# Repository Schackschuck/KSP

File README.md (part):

# KSP Cockpit

Controle físico (painel + joystick + telemetria) para o **Kerbal Space Program 1**, feito do zero com hardware e software próprios.

O objetivo principal é **aprender firmware/embarcados e eletrônica**, e de quebra ter um cockpit de verdade — com direito a um botão que dispara um script de pouso autônomo estilo SpaceX.

---

## Arquitetura

```
 PC com Windows: KSP 1 + servidor kRPC
          ▲
          │  cabo de rede direto, com IP fixo (kRPC, TCP/protobuf)
          │  (pela Wi-Fi de casa durante o desenvolvimento)
          ▼
 Raspberry Pi 4 = computador de bordo ............... bridge/
   • ponte kRPC ⇄ placas, aberta sozinha quando o Pi liga
   • tela multifunção no navegador do tablet ........ bridge/celular/
   • dispara os scripts de voo ....................... scripts/
          ▲                         ▲
          │ USB/serial              │ Wi-Fi de casa
          │ (protocolo próprio)     │ (página da tela, por HTTP)
          ▼                         ▼
 Arduino Mega = I/O do painel    tablet = tela multifunção
 firmware/painel/                (Galaxy Tab S 8.4, no Chrome)
          ▲
          │  SPI + linhas analógicas
          ▼
 Backplane: 12 slots ................................ hardware/backplane/
          ▲
          │  um cabo flat de 16 vias por módulo
          ▼
 Módulos do painel, um por seção .......... hardware/modulo_pequeno/, _medio/ e _grande/
   pequeno: 8 entradas + 8 LEDs (1 × 74HC165 + 1 × 74HC595)
   médio: 16 entradas + 24 LEDs (2 × 74HC165 + 3 × 74HC595), com 12 jacks de korry
   grande: 24 entradas + 16 LEDs (3 × 74HC165 + 2 × 74HC595)
   korry, botões, LEDs, sidestick, acelerador
```

Cada parte tem um papel bem definido:

| Parte | Responsabilidade | Não faz |
|---|---|---|
| **KSP + kRPC** (PC) | Expõe o estado da nave e aceita comandos. | — |
| **Computador de bordo** (Raspberry Pi 4, Python) | Conecta no kRPC pela rede, abre *streams* de telemetria, traduz eventos do painel em comandos do jogo e telemetria em mensagens para o painel. Desenha a tela de telemetria. Dispara os scripts de voo de `scripts/` (ex.: pouso autônomo). | Não lê pino nenhum. |
| **Sidestick** (joystick JH-D400X-R4 no painel, lido pelo Mega) | Manda os 3 eixos e o botão como qualquer controle do painel; a ponte os traduz em comandos do kRPC. | O KSP não enxerga o joystick: tudo passa pela ponte. |
| **Painel** (Arduino Mega, C++) | Lê entradas (com debounce), envia eventos; recebe valores e atualiza LEDs, displays e ponteiros. | **Não sabe que o KSP existe.** É um painel de I/O genérico. |
| **Celular** (opcional, página no navegador) | Mostra a tela multifunção pelo Wi-Fi, com o mesmo protocolo e o mesmo layout, sem precisar da mikromedia. | Não fala com o kRPC nem guarda estado: só desenha o que a ponte manda. |
| **Tela multifunção** (um tablet Galaxy Tab S 8.4, na USB do Pi) | Abre no Chrome a mesma página do celular e desenha as páginas (navball, órbita, recursos, pouso, piloto) com o que a ponte manda; troca de página pelo toque ou sozinha, pelo painel mexido. | Não fala com o kRPC; só mostra o que o computador de bordo manda. |

Durante o desenvolvimento, o mesmo código Python roda no PC — só muda o endereço do servidor kRPC e a porta serial.

### Princípios

- **O LED mostra o estado do jogo, não a posição da chave.** A chave só avisa para onde foi ("SAS para cima"); o computador de bordo decide o que fazer e o jogo confirma. Assim o painel nunca fica dessincronizado (ex.: SAS desligado pelo jogo).
- **Uma tela só, no meio do painel: a tela multifunção.** Os módulos não têm tela própria. Cada módulo que precisa mostrar números (editor de manobras, piloto automático, rendezvous...) tem uma página na tela multifunção. Quando o piloto mexe num módulo, a ponte troca a tela para a página dele; uns segundos depois do último toque no módulo (uns 10 s, a ajustar), a tela volta sozinha para a página de antes, em geral a navball.
- **Protocolo serial em duas versões:**
  - **v0 — texto**, uma mensagem por linha. Fácil de depurar no Serial Monitor.
    ```
    Pi → placa:  ALT 12345      SAS 1      FUEL 73
    placa → Pi:  BTN STAGE 1    SW SAS 0   AX PITCH -312
    ```
  - **v1 — binário**, com enquadramento [COBS](https://en.wikipedia.org/wiki/Consistent_Overhead_Byte_Stuffing), ID de mensagem e CRC. Mais rápido e robusto; vem quando a v0 começar a apertar. É o mesmo protocolo para o Mega e para a mikromedia.
- **Entradas analógicas** (joystick, acelerador) são enviadas a uma taxa fixa, com zona morta e filtro; **entradas digitais** são enviadas só quando mudam.

### Decisões

| Decisão | Por quê |
|---|---|
| **kRPC** em vez de mods de serial (Kerbal Simpit etc.) | Acesso a praticamente tudo do jogo (órbita, estágios, delta-v, autopilot) e permite scripts de voo. A ferramenta não deve ser o limite. |
| **Ponte fora do microcontrolador** em vez do cliente kRPC C-nano | kRPC completo com *streams*; o firmware fica simples e ganha um protocolo próprio — que é onde está o aprendizado de embarcados. |
| **Python** na ponte | Já usado com kRPC antes; o mesmo código roda no PC e no Pi. |
| **Raspberry Pi 4** como computador de bordo | Deixa o cockpit independente do PC (só um cabo de rede): a ponte, os scripts e a voz dos avisos rodam dentro da caixa. |
| **Arduino Mega** para o I/O | O Pi não tem entradas analógicas e o Linux não é tempo real; o Mega tem muitos pinos, trabalha em 5V e é compatível com praticamente todo módulo. |
| **Painel em módulos** com 74HC165 e 74HC595, ligados ao Mega por um backplane | Cada seção do painel é uma placa, montada e testada uma de cada vez. Há três tamanhos (8 entradas e 8 LEDs, 16 e 24, ou 24 e 16), para não montar CI à toa. Cada módulo tem uma etiqueta (chave DIP lida por um 74HC165 a mais), e o Mega reconhece sozinho qual módulo está em cada slot. Os CIs custam poucos reais por módulo, o firmware continua um só e o protocolo com a ponte não muda. Um micro em cada módulo fica para a fase 8. |
| Pinos do Raspberry Pi **não** substituem o Mega | O Pi não tem entradas analógicas, o Linux não é tempo real para encoders e ponteiros, e os pinos de 3,3 V vão direto ao processador: um fio errado nos 5 V queima o Pi. |
| **mikromedia for ARM (LPC2148)** como tela multifunção | Já está na bancada. ARM programado sem framework, com tela touch, microSD e áudio. Começa no protocolo em texto, como o simulador, e passa para o v1 junto com o Mega. |
| **Simulador da tela multifunção** no PC antes do firmware | A ponte, o protocolo e o desenho (navball, números, botões) ficam prontos e testados com o jogo antes da placa; o firmware só precisa copiar o simulador. A placa desenha a partir dos ângulos, porque a imagem pronta não cabe na serial (150 KB por quadro). |
| **Firmware da mikromedia compilado com o LLVM** (clang), e não com o `arm-none-eabi-gcc` | Um compilador só, que já gera código para o ARM7, e um `compilar.py` em Python que roda igual no Windows e no Linux, sem `make`. O `mfd.hex` vai compilado no repositório: para gravar, basta o Flash Magic. |
| **Tela da mikromedia desenhada em faixas de 16 linhas** | Não cabe a tela inteira na RAM (150 KB contra 32 KB), e desenhar direto na tela piscaria. Cada faixa de 10 KB fica pronta na RAM e vai inteira para a tela, então cada ponto é escrito uma vez só. |
| **Orientação e touch da mikromedia ajustados na própria tela** e guardados na flash | O manual não diz a orientação do módulo nem a do touch. Ajustando na tela, o que vier trocado se corrige sem compilar de novo. |
| **Celular como tela**, por uma página web | Funciona já, sem firmware e sem o cabo, em qualquer celular e sem instalar nada. A ponte serve a página e fala com ela por HTTP (Server-Sent Events e POST), só com a biblioteca padrão do Python. O protocolo é o mesmo da placa, então a ponte não muda. |
| **pygame-ce** no lugar do pygame | O pygame original não tem pacote para o Python 3.14; o pygame-ce, mantido pela comunidade, tem e é usado do mesmo jeito (`import pygame`). |
| **Pouso por previsão**: simula a freada até o chão e acha o acelerador por bisseção | Com arrasto, a freada não tem conta fechada. Simular funciona igual em qualquer planeta, com ou sem atmosfera, e refazer a conta 20 vezes por segundo corrige os erros da previsão. O arrasto é medido em voo, e a previsão só usa parte dele, porque ele cai quando a nave fica mais lenta que o som. A guiagem não conhece o kRPC, então é testada numa nave simulada. |
| **Pé da nave medido pelas pernas do trem**, não pela caixa da nave inteira | Nas versões lançadas do kRPC (até a 0.6.0), a caixa de uma peça junta tudo o que está pendurado nela, como a chama do motor ligado. A caixa da nave inteira descia metros abaixo do pé, e a freada terminava alta. |
| **SAS do KSP aponta a nave no pouso**, não o piloto automático do kRPC | O piloto automático do kRPC vem ajustado para levar 3 s até o ângulo pedido e não conta a força do ar. No segundo teste, a nave caindo de ré balançou até 31° na freada. O SAS o jogo ajusta para cada nave. Retrógrado enquanto a nave desce rápido; devagar, perto do chão, o retrógrado pula de um lado para o outro, então no fim o SAS só segura a atitude. |
| **Scripts de voo numa pasta própria** (`scripts/`), fora da ponte | Cada script roda sozinho pela linha de comando, no PC ou no Pi, com ou sem o cockpit. A ponte só dispara o script quando o botão do painel é apertado; o script não depende dela nem do painel. |
| **Script liga segurando o korry 5 s**, e aborta segurando de novo 5 s, sem chave ARM | Um toque sem querer não entrega a nave ao script, e o mesmo gesto aborta, sem procurar outro botão. Economiza a chave ARM com capa e um botão por script. Quem conta o tempo é a ponte, como no encoder do piloto automático, e o korry pisca âmbar enquanto conta. |
| **A ponte abre o script num processo próprio** e aborta com o Ctrl+C | O script continua sendo o mesmo da linha de comando, e o Ctrl+C já corta o motor e devolve a nave. O estado volta pelo UDP, como no fly by wire, e o código de saída diz se a nave pousou. |
| **Um joystick só, no painel** (JH-D400X-R4, um sidestick à direita), com o botão do manche trocando o modo | O cockpit fica como um avião: acelerador na mão esquerda, sidestick na direita. Os 3 eixos cabem nas 3 linhas analógicas de um slot do backplane, e o botão passa pelos modos VOO, CÂMERA e TRANSLAÇÃO, com três luzes. Passando pela ponte, dá para ter zona morta e saber quando o piloto mexe no manche para tirar o controle de um script. O Extreme 3D Pro fica para desenvolver no PC. |
| **Uma tela no meio para todos os módulos**, a tela multifunção, no lugar de um LCD por módulo | Os olhos vão sempre ao mesmo lugar, os painéis ficam menores e só com botões, e sai um LCD por módulo da lista de compras. A página troca sozinha para o módulo em uso e volta depois, então não é preciso escolher a página na mão. Quem decide a troca é a ponte, que já recebe todos os eventos do painel: a tela continua só desenhando. |
| **Korry switches** (botões iluminados com legenda, de avião) onde a luz mostra um estado do jogo | O botão não tem posição, então nunca discorda do jogo: cada toque pede a troca, e a legenda acesa é o estado do jogo. Feitos em casa: a legenda impressa em duas cores encaixa num corpo igual para todos, e a chave e os LEDs vão num suporte impresso atrás, sem placa perfurada ([hardware/korry/](hardware/korry/README.md)). O que não tem estado para mostrar é um botão de 16 mm sem luz. |
| **Cockpit em U, de 766 × 391 mm, com painéis de 125 mm** ([versão B](hardware/construcao.md#cockpit-versão-b)) | Um bloco no meio e duas asas, como num avião, sem painel vazio. Os controles foram juntados em 11 painéis para a caixa não passar de 80 cm; o que não cabe em 125 mm ocupa dois quadrados. O que cada botão faz foi conferido no código-fonte do kRPC antes de desenhar. |
| **A mikromedia de volta**, no lugar da tela de 7" no HDMI do Pi | Sai mais barato: a placa já está na bancada, e o firmware dela já roda na placa, com o jogo. A tela de 2,8" é pequena para o meio do cockpit, que era o motivo da troca pela de 7"; as páginas têm que ser feitas para caber nela. A placa desenha sozinha a partir dos números que a ponte manda, pela USB do Pi. |
| **Um tablet velho como tela**, o Galaxy Tab S 8.4 (SM-T705M, Android 6.0.1), no lugar da mikromedia | Já está na bancada e não serve mais para outra coisa. A tela de 8,4" com toque cabe no painel duplo, e o Chrome do Android 6 roda a mesma página do celular, sem firmware novo. A página chega pela Wi-Fi de casa, vinda do Pi, em HTTP: o tablet só precisa entrar na rede, sem internet. Ele fica no próprio carregador, porque numa USB do Pi a Samsung puxa só uns 0,5 A, que não seguram a tela ligada. A tela de 2,8" da mikromedia ficava pequena no meio do cockpit; ela sai de novo, e o firmware dela continua no repositório. |
| **O mapa da órbita no tablet**, e não no monitor do PC | O monitor fica sempre na vista do foguete. O botão MAPA abre a página MAPA no tablet: a órbita em 3D, as luas, o alvo e o nó de manobra, girada e aproximada pelo toque ([docs/mfd.md](docs/mfd.md#a-página-mapa)). O mapa do jogo continua lá, mas o cockpit não precisa dele. |
| **Pi ligado no PC por um cabo de rede direto**, com IP fixo dos dois lados, no lugar da Wi-Fi | A ida e volta pelo cabo fica abaixo de 0,5 ms e quase não varia; pela Wi-Fi são de 2 a 10 ms, com picos de 20 a 100 ms, e a variação atrapalha o fly by wire. Não depende do roteador, os endereços não mudam, e o PC e o Pi continuam na internet pela Wi-Fi. No PC só roda o KSP com o kRPC: a ponte abre sozinha no Pi e espera o jogo. Os 1 a 2 quadros de atraso do próprio kRPC continuam ([docs/setup-pi.md](docs/setup-pi.md#8-cabo-de-rede-direto-até-o-pc)). |
| **Recursos na tela multifunção**, sem as barras de LED | Saem o MAX7219, as 5 barras de 10 LEDs e a fiação delas, e a tela já recebe tudo da ponte. O combustível, o oxidante, o monopropelente e a eletricidade vão para uma página da tela. |
| **Caixa em MDF cortado a laser, com peças impressas em 3D** | A laser do colégio faz as peças planas e grandes (paredes, painéis com legendas); a impressora de casa, as pequenas e complicadas (korry, knobs, suportes). Cada seção é um painel removível com o seu módulo atrás. |
| **Fly by wire com a lei de um caça**: o manche pede carga (g) e velocidade de rolagem, e não mexe nas superfícies | A primeira versão movia um ponto na navball, e o avião ia até ele: estável, mas lenta e "interventora" no jogo (o voo gravado mostrou o avião respondendo quase 1 s depois e seguindo o ponto depois de o manche ser solto). Pedindo carga e rolagem, o avião responde na hora, e soltar o manche segura o caminho e a inclinação. O piloto automático pede um caminho, e o FBW calcula a carga e a inclinação para chegar nele. |
| **Ganhos do FBW divididos pela autoridade do avião** (torque disponível ÷ inércia, informados pelo kRPC) | A força das superfícies cresce com o quadrado da velocidade: um ganho fixo, bom na decolagem, faz o avião balançar rápido, e cada avião precisaria do seu. Nos testes, o FBW segura o avião com a autoridade informada errada pela metade ou pelo dobro. |
| **Scripts mandam marcadores à ponte da tela por UDP**, com a própria linha do protocolo da tela | O script continua rodando sozinho: sem a ponte aberta, a linha se perde e nada acontece. A ponte só confere e repassa. |
| **Avisos de voo (GPWS) na ponte da tela, falados no Pi** | A ponte já lê o jogo o tempo todo, então avisa em qualquer avião, com ou sem o fly by wire. A voz sai por um alto-falante USB no Pi, pelo `espeak-ng` ou por gravações; o áudio da mikromedia (VS1053) fica para os alarmes da própria tela. |
| **O `fbw.py` lê o joystick sozinho**, por enquanto | A ponte ainda não lê o joystick. Quando ler, a leitura passa para ela, e o script recebe o manche da ponte. |
| **ESP32** fica para depois | Candidato a painel sem fio ou módulo extra (fase 8). |

### Estrutura planejada do repositório

```
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
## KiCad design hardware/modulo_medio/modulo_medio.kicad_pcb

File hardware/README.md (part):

# Hardware

Esquemáticos do painel, feitos no KiCad. Cada pasta tem também um PDF do esquema, que dá para ver sem instalar nada.

| Pasta | Placa | CIs |
|---|---|---|
| [`modulo_pequeno/`](modulo_pequeno/) | Módulo pequeno: 8 entradas e 8 LEDs ([PDF](modulo_pequeno/modulo_pequeno.pdf)) | etiqueta + 1 × 74HC165, 1 × 74HC595 |
| [`modulo_medio/`](modulo_medio/) | Módulo médio: 16 entradas e 24 LEDs, com 12 jacks de korry ([PDF](modulo_medio/modulo_medio.pdf), [PCB](#pcb-do-módulo-médio)) | etiqueta + 2 × 74HC165, 3 × 74HC595 |
| [`modulo_grande/`](modulo_grande/) | Módulo grande: 24 entradas e 32 LEDs ([PDF](modulo_grande/modulo_grande.pdf)) | etiqueta + 3 × 74HC165, 4 × 74HC595 (o esquema ainda tem 2: ver [Próximos passos](#próximos-passos)) |
| [`backplane/`](backplane/) | Backplane: liga até 12 módulos ao Mega ([PDF](backplane/backplane.pdf)) | — |

A parte física (carcaça, aparência, os painéis da versão B e o sidestick) está em [construcao.md](construcao.md). Peças feitas em casa e usadas em vários painéis têm pasta própria, com a ficha e os desenhos: [`korry/`](korry/README.md). A [identidade visual](identidade_visual.md) diz como todo painel tem que parecer, e os desenhos dos painéis são gerados por código em [`desenho/`](desenho/README.md).

As três placas de módulo usam o mesmo cabo flat e encaixam em qualquer slot. Cada uma tem uma **etiqueta**, um 74HC165 a mais ligado a uma chave DIP de 8 vias: é por ela que o Mega descobre sozinho qual módulo está em cada slot.

## Como abrir

1. Instale o KiCad 7 ou mais novo e abra o `.kicad_pro` de cada pasta.
2. Os arquivos estão no formato do KiCad 7. Uma versão mais nova avisa que vai converter o arquivo ao salvar: pode aceitar.
3. Os símbolos estão embutidos no esquema. As footprints já estão escolhidas (DIP-16 com soquete, IDC 2x8, chave DIP, barras de pinos). O módulo médio já tem a PCB pronta para fabricar ([abaixo](#pcb-do-módulo-médio)); as outras placas ficam para a fase 7.
4. Ao abrir, rode o verificador de regras elétricas: menu **Inspecionar → Verificador de Regras Elétricas (ERC)**.

## Como tudo se liga

```
Mega ──(7 fios)── Backplane ── slot 1 ──(cabo flat)── módulo
                            ├─ slot 2 ──(cabo flat)── módulo
                            └─ ... até o slot 12
```

- **O Mega nunca liga direto nos módulos,** só no backplane: 5 sinais, +5V e GND.
- **Os pinos do Mega não aumentam com o número de módulos.** Os sinais seguem de módulo em módulo, numa fila.
- **As entradas de todos os módulos formam uma única cadeia de 74HC165,** que termina no MISO do Mega.
- **As saídas formam uma única cadeia de 74HC595,** que começa no MOSI.
- **Só os módulos com joystick ou acelerador** precisam de mais fios até o Mega: 3 analógicos por slot.

### Cabo flat (IDC 2x8, igual no módulo e no slot)

| Pino | Sinal | Pino | Sinal |
|---|---|---|---|
| 1 | +5V | 2 | GND |
| 3 | SCK | 4 | GND |
| 5 | PL (carrega as entradas) | 6 | RCLK (atualiza os LEDs) |
| 7 | SIN165 (vem do slot seguinte) | 8 | SOUT165 (vai para o Mega) |
| 9 | SIN595 (vem do Mega) | 10 | SOUT595 (vai para o slot seguinte) |
| 11 | AN_A | 12 | GND |
| 13 | AN_B | 14 | AN_C |
| 15 | +5V | 16 | GND |

### Ligação ao Mega

| Sinal | Pino do Mega | Observação |
|---|---|---|
| SCK | D52 | SPI |
| MOSI | D51 | Entra na cadeia de 74HC595 |
| MISO | D50 | Sai da cadeia de 74HC165 |
| PL | D49 | |
| RCLK | D48 | |
| Analógicos dos slots 1 a 5 | A0 a A14 | Slot k: A(3k−3), A(3k−2), A(3k−1) |
| 5V | 5V | Só com JP1 em 1-2 |
| GND | GND | Sempre ligado, mesmo com fonte externa |

Não use o D53 (SS) como entrada: se ele for a 0, o SPI do Mega sai do modo mestre. O `SPI.begin()` já o deixa como saída.

### Regras do backplane

1. **Módulos em slots seguidos,** a partir do slot 1, sem buracos. O Mega para de ler no primeiro slot vazio.
2. **A ordem dos módulos não importa:** cada um se identifica pela etiqueta.
3. **Módulos com joystick ou acelerador vão nos slots 1 a 5,** os únicos com linhas analógicas.
4. **JP1 escolhe de onde vem o +5V dos módulos:**
   - **1-2:** 5 V do Mega. Serve para poucos módulos, com o Mega alimentado pela USB.
   - **2-3:** fonte externa de 5 V no borne J3. É para o painel completo.
   - Use um jumper só: ele liga 1-2 ou 2-3, nunca as duas fontes juntas.
5. **Encaixe e tire módulos com o painel desligado.** O conector do cabo flat não garante que o GND encosta antes dos sinais. Ao ligar, o Mega reconhece sozinho o que estiver encaixado.

## Primeiro teste: um módulo direto no Mega

Dá para testar um módulo antes de montar o backplane, ligando o conector J1 do módulo direto no Mega com 8 jumpers:

| J1 do módulo | Mega |
|---|---|
| 1 (+5V) | 5V |
| 2 (GND) | GND |
| 3 (SCK) | D52 |
| 5 (PL) | D49 |
| 6 (RCLK) | D48 |
| 8 (SOUT165) | D50 (MISO) |
| 9 (SIN595) | D51 (MOSI) |
| 7 (SIN165) | GND: marca o fim da fila, como faria um slot vazio |

Os pinos 4, 12 e 16 são GND repetidos, e 15 é +5V repetido: com um cabo curto não precisam de fio. O 10 (SOUT595) fica solto. Os analógicos (11, 13 e 14) vão em A0, A1 e A2, se o módulo tiver joystick.

## Etiqueta: como o Mega reconhece cada módulo

A etiqueta é o primeiro byte que o Mega lê de cada módulo.

**O byte da etiqueta:**
- Cada chave DIP ligada (ON) põe o bit correspondente em 1. A chave k é o bit k−1.
- O Mega inverte o byte lido, porque a chave liga a entrada ao GND.
- **Bits 7 e 6 = tamanho da placa:** 01 pequena, 10 média, 11 grande. É por eles que o Mega sabe quantos bytes vêm depois.
- **Bits 5 a 0 = número da seção:** de 1 a 62, e diz qual módulo é.

**Valores reservados:**
- **Tudo ligado (byte 0xFF depois de inverter):** é o que o Mega lê num slot vazio, graças aos pull-downs do backplane. Quer dizer "acabou a fila".
- **Tudo desligado (0x00):** etiqueta esquecida; o Mega avisa em vez de adivinhar.

**Como o Mega lê a fila:**
1. Lê a etiqueta do slot 1.
2. Pelo tamanho, sabe quantos bytes de entrada pular: 1, 2 ou 3.
3. Lê a etiqueta do slot 2, e assim por diante, até achar a marca de fim.

Assim, não existe tabela de slots no firmware. O Mega avisa a ponte qual módulo está em cada slot, e a ponte sabe o que cada entrada e cada LED daquele módulo faz no jogo.

### Qual placa e qual etiqueta em cada seção

| Seção do painel | Entradas | LEDs | Placa | Número | Chaves DIP em ON |
|---|---|---|---|---|---|
| [Ação executiva](construcao.md#ação-executiva) (STAGE, ABORT e os 6 scripts) | 8 | 14 | média | 1 | 1, 8 |
| [Tempo](construcao.md#tempo) | 9 | 1 | média | 2 | 2, 8 |
| [Sidestick](construcao.md#sidestick) (3 eixos analógicos) | 1 | 3 | pequena, slots 1 a 5 | 3 | 1, 2, 7 |
| [Acelerador](construcao.md#acelerador) (alavanca analógica, trem, freios e luzes) | 3 | 3 | pequena, slots 1 a 5 | 5 | 1, 3, 7 |
| [EVA](construcao.md#eva) | 6 | 2 | pequena | 6 | 2, 3, 7 |
| [Voo](construcao.md#painel-de-sistemas-de-controle) (SAS, RCS, FBW, o encoder AJUSTE, as luzes do piloto e os avisos) | 18 | 31 | grande | 7 | 1, 2, 3, 7, 8 |
| [Action groups](construcao.md#action-groups) (1 a 8 e as peças) | 12 | 4 | média | 8 | 4, 8 |
| [Câmera](construcao.md#câmera) | 5 | 2 | pequena | 9 | 1, 4, 7 |
| [Navegação](construcao.md#navegação) | 8 | 0 | pequena | 10 | 2, 4, 7 |
| [Editor de manobras](construcao.md#painel-do-editor-de-manobras) | 14 | 3 | média | 12 | 3, 4, 8 |

São 10 módulos da [versão B do cockpit](construcao.md#cockpit-versão-b): 5 pequenos, 4 médios e 1 grande, e sobram 2 slots. A tela multifunção é um tablet, sem controles, e não tem módulo: o número 4 ficou livre. O sidestick e o acelerador vão nos slots 1 a 5, os únicos com linhas analógicas: o sidestick usa as três (X, Y e torção), o acelerador uma. As seções da mesma placa podem ficar longe uma da outra no painel: os fios dos botões até a placa podem ter uns 30 cm.

Os números 3, 4, 6, 9 e 11 mudaram de seção com a versão B: antes eram os analógicos de rotação e translação, a telemetria, a EVA e a câmera. O firmware ainda não lê as etiquetas, então nada no código muda.

## No módulo

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
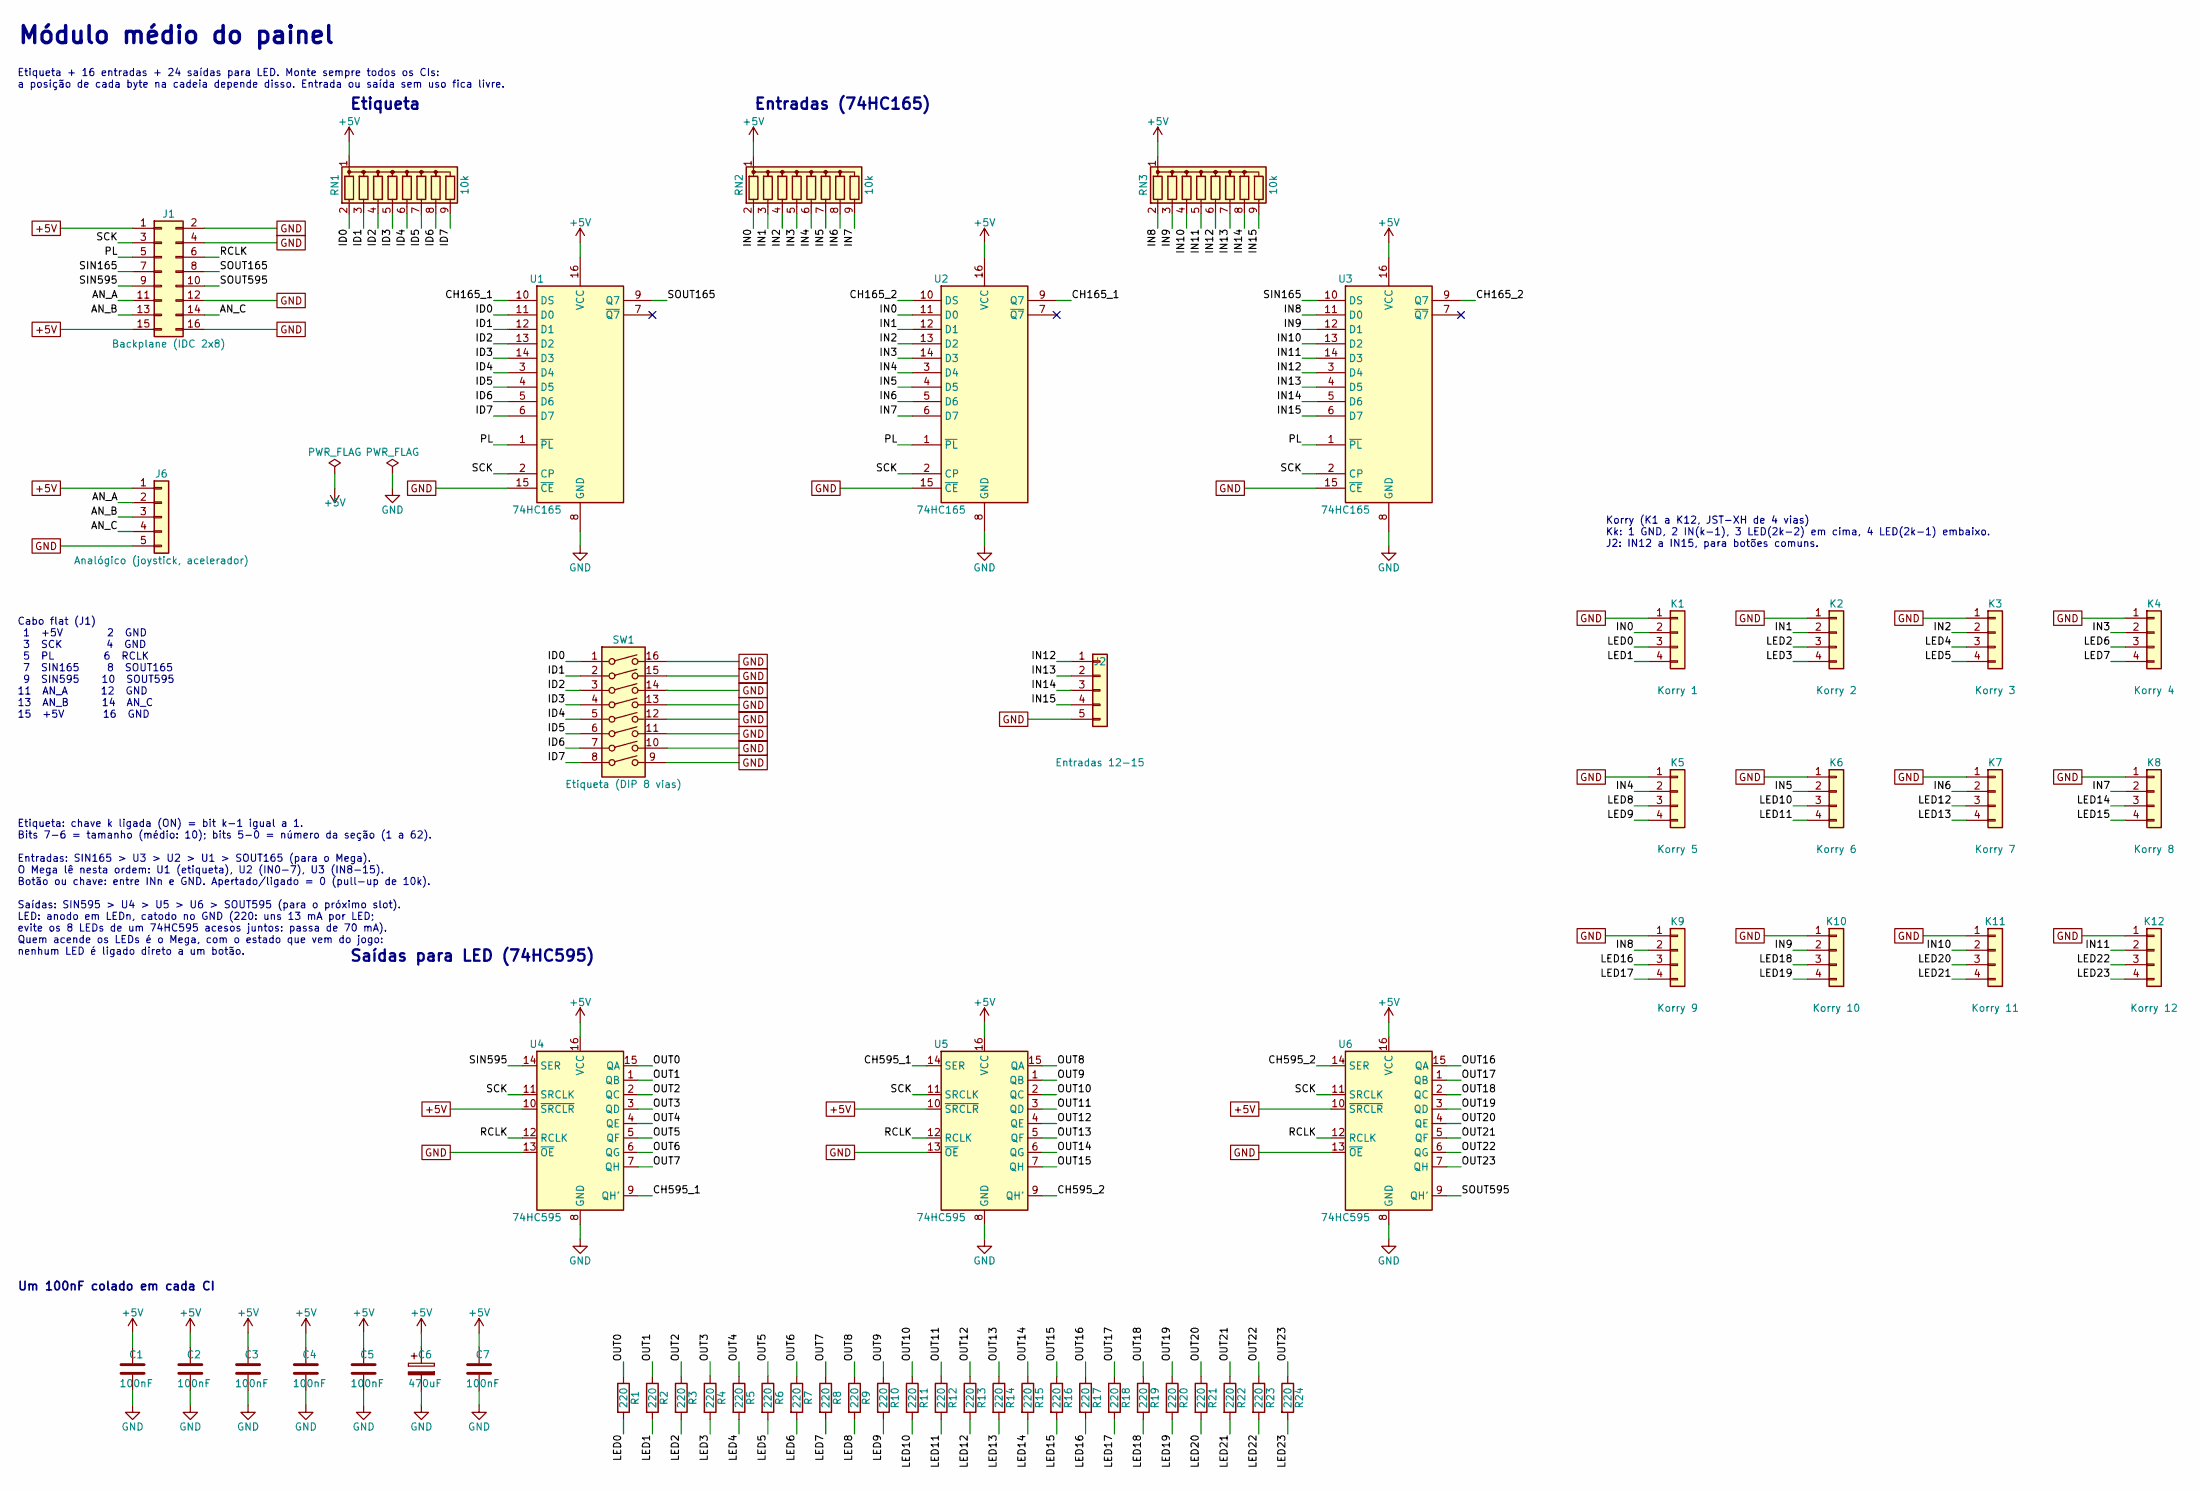
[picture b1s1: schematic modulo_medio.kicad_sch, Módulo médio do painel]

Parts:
C1, C2, C3, C4, C5, C7: 100nF; C_Disc_D5.0mm_W2.5mm_P5.00mm
C6: 470uF; CP_Radial_D10.0mm_P5.00mm
J1: Backplane (IDC 2x8); IDC-Header_2x08_P2.54mm_Vertical
J2: Entradas 12-15; PinHeader_1x05_P2.54mm_Vertical
J6: Analógico (joystick, acelerador); PinHeader_1x05_P2.54mm_Vertical
K1: Korry 1; JST_XH_B4B-XH-A_1x04_P2.50mm_Vertical
K2: Korry 2; JST_XH_B4B-XH-A_1x04_P2.50mm_Vertical
K3: Korry 3; JST_XH_B4B-XH-A_1x04_P2.50mm_Vertical
K4: Korry 4; JST_XH_B4B-XH-A_1x04_P2.50mm_Vertical
K5: Korry 5; JST_XH_B4B-XH-A_1x04_P2.50mm_Vertical
K6: Korry 6; JST_XH_B4B-XH-A_1x04_P2.50mm_Vertical
K7: Korry 7; JST_XH_B4B-XH-A_1x04_P2.50mm_Vertical
K8: Korry 8; JST_XH_B4B-XH-A_1x04_P2.50mm_Vertical
K9: Korry 9; JST_XH_B4B-XH-A_1x04_P2.50mm_Vertical
K10: Korry 10; JST_XH_B4B-XH-A_1x04_P2.50mm_Vertical
K11: Korry 11; JST_XH_B4B-XH-A_1x04_P2.50mm_Vertical
K12: Korry 12; JST_XH_B4B-XH-A_1x04_P2.50mm_Vertical
R1, R2, R3, R4, R5, R6, R7, R8, R9, R10, R11, R12, R13, R14, R15, R16, R17, R18, R19, R20, R21, R22, R23, R24: 220; R_Axial_DIN0207_L6.3mm_D2.5mm_P7.62mm_Horizontal
RN1, RN2, RN3: 10k; R_Array_SIP9
SW1: Etiqueta (DIP 8 vias); SW_DIP_SPSTx08_Slide_9.78x22.5mm_W7.62mm_P2.54mm
U1, U2, U3: 74HC165; DIP-16_W7.62mm_Socket
U4, U5, U6: 74HC595; DIP-16_W7.62mm_Socket

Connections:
+5V: C1.1, C2.1, C3.1, C4.1, C5.1, C6.1, C7.1, J1.1, J1.15, J6.1, RN1.1 (common), RN2.1 (common), RN3.1 (common), U1.16 (VCC), U2.16 (VCC), U3.16 (VCC), U4.10 (~SRCLR), U4.16 (VCC), U5.10 (~SRCLR), U5.16 (VCC), U6.10 (~SRCLR), U6.16 (VCC)
/AN_A: J1.11, J6.2
/AN_B: J1.13, J6.3
/AN_C: J1.14, J6.4
/CH165_1: U1.10 (DS), U2.9 (Q7)
/CH165_2: U2.10 (DS), U3.9 (Q7)
/CH595_1: U4.9 (QH'), U5.14 (SER)
/CH595_2: U5.9 (QH'), U6.14 (SER)
/ID0: RN1.2 (R1), SW1.1, U1.11 (D0)
/ID1: RN1.3 (R2), SW1.2, U1.12 (D1)
/ID2: RN1.4 (R3), SW1.3, U1.13 (D2)
/ID3: RN1.5 (R4), SW1.4, U1.14 (D3)
/ID4: RN1.6 (R5), SW1.5, U1.3 (D4)
/ID5: RN1.7 (R6), SW1.6, U1.4 (D5)
/ID6: RN1.8 (R7), SW1.7, U1.5 (D6)
/ID7: RN1.9 (R8), SW1.8, U1.6 (D7)
/IN0: K1.2, RN2.2 (R1), U2.11 (D0)
/IN1: K2.2, RN2.3 (R2), U2.12 (D1)
/IN2: K3.2, RN2.4 (R3), U2.13 (D2)
/IN3: K4.2, RN2.5 (R4), U2.14 (D3)
/IN4: K5.2, RN2.6 (R5), U2.3 (D4)
/IN5: K6.2, RN2.7 (R6), U2.4 (D5)
/IN6: K7.2, RN2.8 (R7), U2.5 (D6)
/IN7: K8.2, RN2.9 (R8), U2.6 (D7)
/IN8: K9.2, RN3.2 (R1), U3.11 (D0)
/IN9: K10.2, RN3.3 (R2), U3.12 (D1)
/IN10: K11.2, RN3.4 (R3), U3.13 (D2)
/IN11: K12.2, RN3.5 (R4), U3.14 (D3)
/IN12: J2.1, RN3.6 (R5), U3.3 (D4)
/IN13: J2.2, RN3.7 (R6), U3.4 (D5)
/IN14: J2.3, RN3.8 (R7), U3.5 (D6)
/IN15: J2.4, RN3.9 (R8), U3.6 (D7)
/LED0: K1.3, R1.2
/LED1: K1.4, R2.2
/LED2: K2.3, R3.2
/LED3: K2.4, R4.2
/LED4: K3.3, R5.2
/LED5: K3.4, R6.2
/LED6: K4.3, R7.2
/LED7: K4.4, R8.2
/LED8: K5.3, R9.2
/LED9: K5.4, R10.2
/LED10: K6.3, R11.2
/LED11: K6.4, R12.2
/LED12: K7.3, R13.2
/LED13: K7.4, R14.2
/LED14: K8.3, R15.2
/LED15: K8.4, R16.2
/LED16: K9.3, R17.2
/LED17: K9.4, R18.2
/LED18: K10.3, R19.2
/LED19: K10.4, R20.2
/LED20: K11.3, R21.2
/LED21: K11.4, R22.2
/LED22: K12.3, R23.2
/LED23: K12.4, R24.2
/OUT0: R1.1, U4.15 (QA)
/OUT1: R2.1, U4.1 (QB)
/OUT2: R3.1, U4.2 (QC)
/OUT3: R4.1, U4.3 (QD)
/OUT4: R5.1, U4.4 (QE)
/OUT5: R6.1, U4.5 (QF)
/OUT6: R7.1, U4.6 (QG)
/OUT7: R8.1, U4.7 (QH)
/OUT8: R9.1, U5.15 (QA)
/OUT9: R10.1, U5.1 (QB)
/OUT10: R11.1, U5.2 (QC)
/OUT11: R12.1, U5.3 (QD)
/OUT12: R13.1, U5.4 (QE)
/OUT13: R14.1, U5.5 (QF)
/OUT14: R15.1, U5.6 (QG)
/OUT15: R16.1, U5.7 (QH)
/OUT16: R17.1, U6.15 (QA)
/OUT17: R18.1, U6.1 (QB)
/OUT18: R19.1, U6.2 (QC)
/OUT19: R20.1, U6.3 (QD)
/OUT20: R21.1, U6.4 (QE)
/OUT21: R22.1, U6.5 (QF)
/OUT22: R23.1, U6.6 (QG)
/OUT23: R24.1, U6.7 (QH)
/PL: J1.5, U1.1 (~PL), U2.1 (~PL), U3.1 (~PL)
/RCLK: J1.6, U4.12 (RCLK), U5.12 (RCLK), U6.12 (RCLK)
/SCK: J1.3, U1.2 (CP), U2.2 (CP), U3.2 (CP), U4.11 (SRCLK), U5.11 (SRCLK), U6.11 (SRCLK)
/SIN165: J1.7, U3.10 (DS)
/SIN595: J1.9, U4.14 (SER)
/SOUT165: J1.8, U1.9 (Q7)
/SOUT595: J1.10, U6.9 (QH')
GND: C1.2, C2.2, C3.2, C4.2, C5.2, C6.2, C7.2, J1.2, J1.4, J1.12, J1.16, J2.5, J6.5, K1.1, K2.1, K3.1, K4.1, K5.1, K6.1, K7.1, K8.1, K9.1, K10.1, K11.1, K12.1, SW1.9, SW1.10, SW1.11, SW1.12, SW1.13, SW1.14, SW1.15, SW1.16, U1.8 (GND), U1.15 (~CE), U2.8 (GND), U2.15 (~CE), U3.8 (GND), U3.15 (~CE), U4.8 (GND), U4.13 (~OE), U5.8 (GND), U5.13 (~OE), U6.8 (GND), U6.13 (~OE)

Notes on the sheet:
Módulo médio do painel
Etiqueta + 16 entradas + 24 saídas para LED. Monte sempre todos os CIs: a posição de cada byte na cadeia depende disso. Entrada ou saída sem uso fica livre.
Etiqueta
Entradas (74HC165)
Saídas para LED (74HC595)
Um 100nF colado em cada CI
Cabo flat (J1) 1 +5V 2 GND 3 SCK 4 GND 5 PL 6 RCLK 7 SIN165 8 SOUT165 9 SIN595 10 SOUT595 11 AN_A 12 GND 13 AN_B 14 AN_C 15 +5V 16 GND
Etiqueta: chave k ligada (ON) = bit k-1 igual a 1. Bits 7-6 = tamanho (médio: 10); bits 5-0 = número da seção (1 a 62). Entradas: SIN165 > U3 > U2 > U1 > SOUT165 (para o Mega). O Mega lê nesta ordem: U1 (etiqueta), U2 (IN0-7), U3 (IN8-15). Botão ou chave: entre INn e GND. Apertado/ligado = 0 (pull-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
Korry (K1 a K12, JST-XH de 4 vias) Kk: 1 GND, 2 IN(k-1), 3 LED(2k-2) em cima, 4 LED(2k-1) embaixo. J2: IN12 a IN15, para botões comuns.

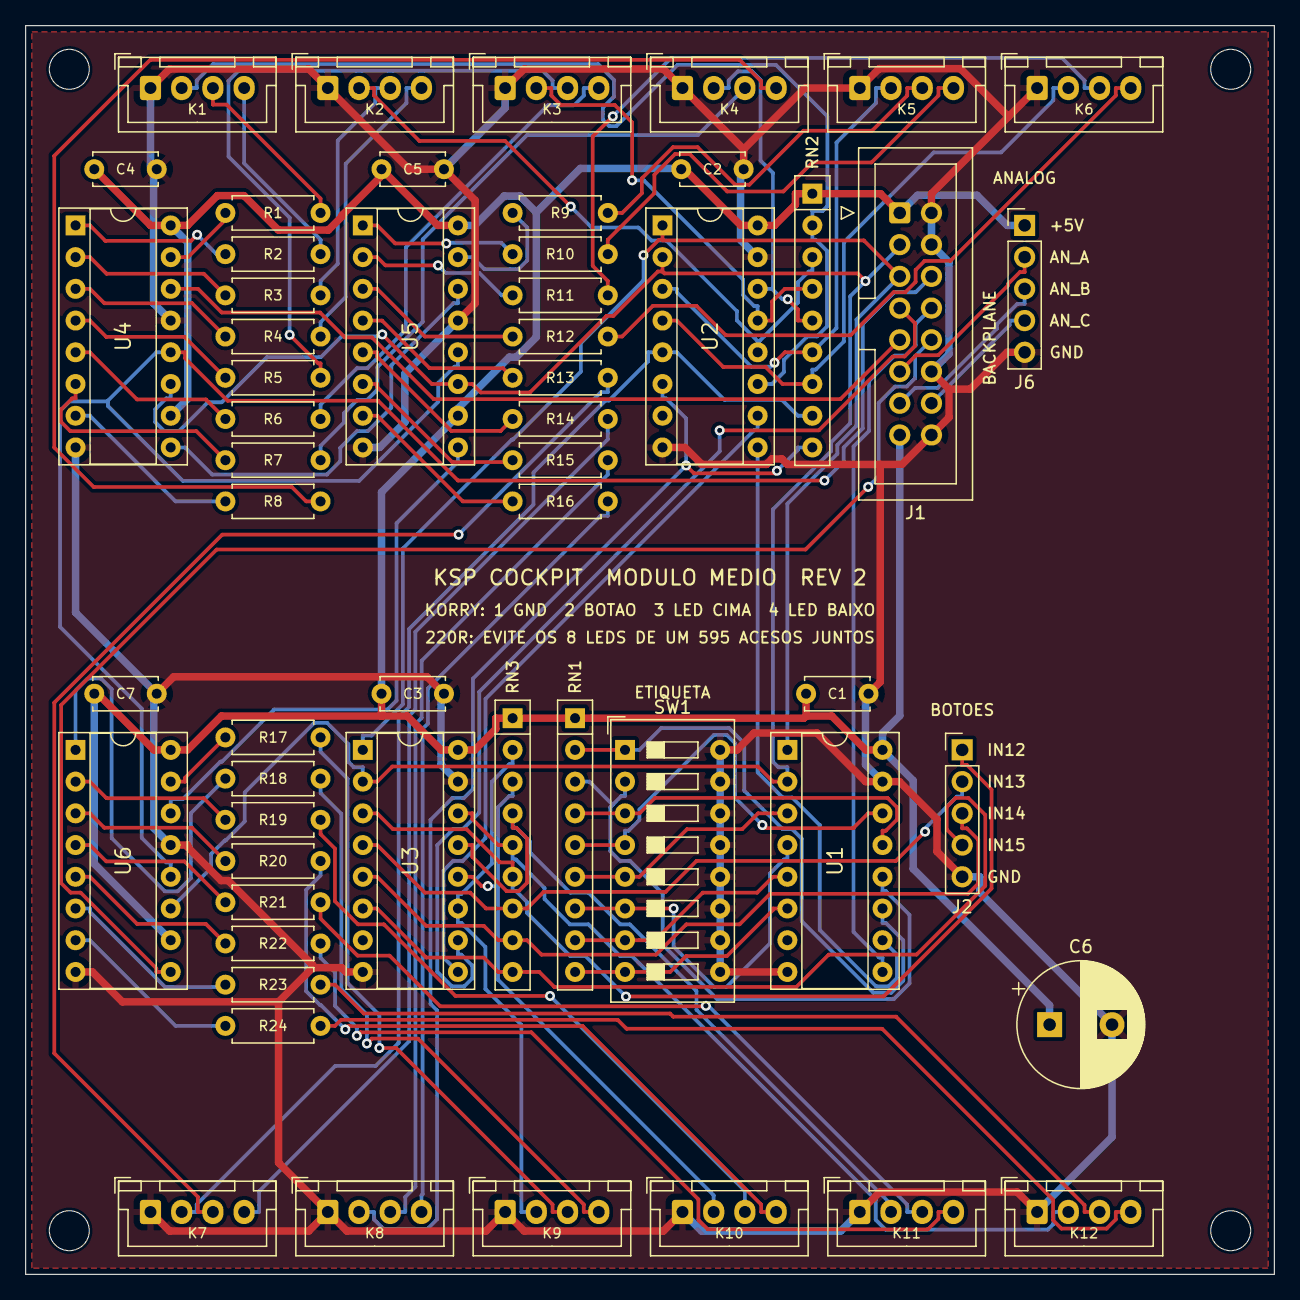
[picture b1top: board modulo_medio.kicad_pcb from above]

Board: 2 copper layers, 100.0 x 100.0 mm, 60 parts (0 on the bottom side), 88 nets.

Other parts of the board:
H1, H2, H3, H4: MountingHole_3.2mm_M3
